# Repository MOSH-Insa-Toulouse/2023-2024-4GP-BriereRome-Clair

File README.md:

# 2023-2024-4GP-BriereRome-Clair
Projet Capteur de Jules et Gabriel 
# Projet Capteur
## Contexte <br>
Nous avons rélalisé ce projet dans le cadre de notre cours de MOSH (Microcontroleur en Open Source Hardware) à l'INSA Toulouse en 4ème année au sein du département de Génie Physique. <br>
L'objectif de ce projet est de tester les caractéristiques d'un capteur de flexion en graphite. <br>
## Somaire
### [1. Présentation Générale](#pg)
### [2. L'électronique analogique](#ea)
### [3. KiCad](KiCad)
### [4. L'Arduino](#dudu)
### [5. L'Application](#app)
### [6. Résultats et datasheet](#res) 

# 1. Présentation Générale <a name="pg">
Voici ci-dessous un schéma de notre projet qui permet de visualiser le lien entre chaque partie. <br>
```mermaid
    graph TD;
    classDef PCB1 fill:pink,color:black,stroke:black;
    classDef App fill:lightblue,color:black,stroke:black;
    B((Carte Arduino))-->Module_BT;
    Boutons-->B((Carte Arduino));
    Ampli-->B((Carte Arduino));
    Potentiomètre -.- OLED;
    Potentiomètre-->Ampli; 
    D[Capteur Graphite]-->Ampli;
    Boutons -.- Potentiomètre;
    B((Carte Arduino))-->Potentiomètre;
    Module_BT -.-> appli;
    B((Carte Arduino))-->OLED;
    A[Flex Sensor]-->B((Carte Arduino));
    PCB
    class Ampli PCB1;
    class Potentiomètre PCB1;
    class Boutons PCB1;
    class OLED PCB1;
    class Module_BT PCB1;
    class Appli App;
    class PCB PCB1;
``` 
Afin de mesurer la flexion de notre capteur graphite nous mesurons sa resistance. Cependant, sa resitance étant très grande, le signal à mesurer est très faible. Nous utilisons donc un amplificateur pour augmenter le signal et qu'il soit ainsi mesurable. Nous utilisons ensuite une carte arduino uno pour mesurer ce signal et le transmettre via bluetooth à une application mobile. Nous utilisons aussi des boutons et un afficheur OLED afin de changer la valeur d'un potententiomètre digital qui module le gain de l'amplificateur. <br>

# 2. L'electronique analogique <a name="ea">
La résistance de notre capteur en graphite varie en fonction de sa flexion. Nous cherchons donc à mesurer les variations de résistance de ce capteur. Cependant il n'y a que des entrée analogique de tension, et les variations de signal sont très petites, il nous faut donc utiliser un circuit amplificateur transimpédence afin d'obtenir une variation de tension mesurable par les convertisseur Analogique-Numérique de l'Arduino.

La résistance du capteur varie en fonction de sa déformation. On impose une tension à ses bornes et on détecte donc une variation de courrant. On fait passer ce courrant dans une résistance de shunt vers la masse, la tension au borne de cette résistance de shunt varie donc avec la déformation du capteur. C'est cette tension que l'on va amplifier.
<br>
Schéma de l'amplificateur : <br>
 <br>
La résistance R2 est remplacée par un potentiomètre digital afin de pouvoir régler le gain de l'amplificateur.

# 3. KiCad : [ici pour les docs](https://github.com/MOSH-Insa-Toulouse/2023-2024-4GP-BriereRome-Clair/tree/main/Shield) <a name="KiCad">
Nous avons réalisé un PCB en utilisant l'application KiCad8. Pour ce faire, nous avons repris le schéma éléctrique decrit ci-dessus. <br>
Nos contraintes etaient les suivantes:
* Largeur de la piste : 0,5 mm minimum
* Isolation des pistes : 0.5mm minimum
* Bluetooth, OLED, Connecteurs (header) : pad à 1mm de diamètre, ovale 2*2.54mm
* Résistance, condensateur, support AOP : Pad à 0.8mm de diamètre, Cercle 2.54mm
* Support AOP, Pot Digital : pad n°1 rectangulaire, les autres ovales ou ronds

Nous avons créé la plupart des emprintes pour les rajouter au PCB. Elles sont disponibles dans nos fichiers. <br>
Une fois le document complété, nous avons imprimé le PCB et avons soudé chacun des composants. <br>
    <br>
   Partie Schématique: <br>
    <br>
   <br>
   Partie PCB : <br>
    <br>

# 4. L'Arduino : [ici pour le code](https://github.com/MOSH-Insa-Toulouse/2023-2024-4GP-BriereRome-Clair/blob/main/Projet_capt.ino) <a name="dudu">
## Présentation générale
Le programme Arduino permet de réaliser 4 fonctions :
* ***Régalage*** du calibre de l'amplificateur avec **3 boutons**
* ***Affichage*** du choix sur un **ecran OLED**
* ***Acquisition*** des mesurese du **flex sensor**
* ***Communication*** vers une appli Android via **bluetooth**
Le code est modulaire, chaque fonctionnalité est assurée par une fonction indépendante.

## Détail sur les bouton
On utilise 3 boutons (+, - et ok) pour choisir la valeur du gain. La boucle générale met assez de temps à s'exécuter pour ne pas avopir à gérer le débouncing des boutons. On a aussi implémenter un timer qui permet que la valeur de change pas trop vite en cas d'appuie long.
Le code utilise 2 variables (valeur séléctionnée et valeur validée)

## Détail sur l'écran
Nous avons utilisé très simplement la librairie ecranOLED

## Détail sur le potentiomètre numérique
Ce composant communique avec le protocole SPI, nous avons donc utilisé la librairie SPI.

## Détail sur l'acquisition des données
Nous avons fait une lecture analogique sur les entrée puis utilisé map pour que les données soient transférable via le module bluetooth en un seul octet.

## Détail sur la communication
Nous avons écrit les données sur un port série relié au module bluetooth.

# 5. L'Application <a name="app">
Afin de communiquer avec l'adruino, nous avons créé une application en utilisant "MIT app inventor".
## Présentation générale
Notre application comporte : <br>
* 2 graphiques :
    * 1 pour le capteur graphite
    * 1 pour le flex sensor
* 2 afficheurs numériques avec des valeurs entre 0 et 255
  * 1 pour le capteur graphite
  * 1 pour le flex sensor
* 1 bouton de sélection Bluetooth
* 1 bouton de reset pour les graphiques
  <br>
    
    <br>
## Partie 1 : Sélection du périphérique Bluetooth
En cliquant sur le bouton "select bluetooth", vous pouvez ouvrir une liste déroulante et selectionner le bluetooth correspondant au module bluetooth utillisé sur le PCB.

## Partie 2 : Reception des données
Le fait de sélectionner un Bluetooth déclenche une horloge qui va séquencer la reception de données. <br>
La boucle de l'horloge verifie si des données sont disponibles. Si il y en a, elle met chacune des deux valeurs (Flex sensor et capteur graphite) dans une variable. <br>

## Partie 3 : Affichage graphique
Afin de rendre les données facilement lisibles, nous avons décidé d'utiliser des graphiques. Pour cela nous avons utilisé les chart2D. <br>
Afin de recentrer automatiquement le graphique, nous attendons d'avoir le bon nombre de mesures et utilisons ensuite la fonction SetDomain pour décaler le graphique. Le bouton reset permet de remettre l'echelle à 0.

# 6. Résultats et datasheet <a name="res">
### Objectifs
Nous avons monté un banc de test afin d'etudier l'influence du type de crayon utilisé sur les performances du capteur et regarder la variation de résistance. <br>
### Méthode
Pour cela nous avons utilisé des cercles de diamètre differnent (2cm, 3cm, 4cm et 5cm). La déformation est calculée selon l'expression suivante : $\varepsilon = \frac{D}{e}$ avec $D$ diamètre du demi-cercle et épaisseur du papier. <br>
Nous avons ensuite exprimé la variation de résistance en fonction de la deformation. <br>
### Résultats
Nous avons obtenu les courbes ci-dessous. Nous observons que la variation est lineaire et que le type de crayon a une forte influence. Les crayons plus durs ("hard") semblent avoir une plus grande sensibilité que les crayons doux. <br>
Ce resultat est le même en compression et en tension. <br>
<br>

<br>
### Datasheet
Afin de synthétiser nos résultats, nous avons fait une datasheet disponible [ici](https://github.com/MOSH-Insa-Toulouse/2023-2024-4GP-BriereRome-Clair/blob/main/Datasheet.docx).

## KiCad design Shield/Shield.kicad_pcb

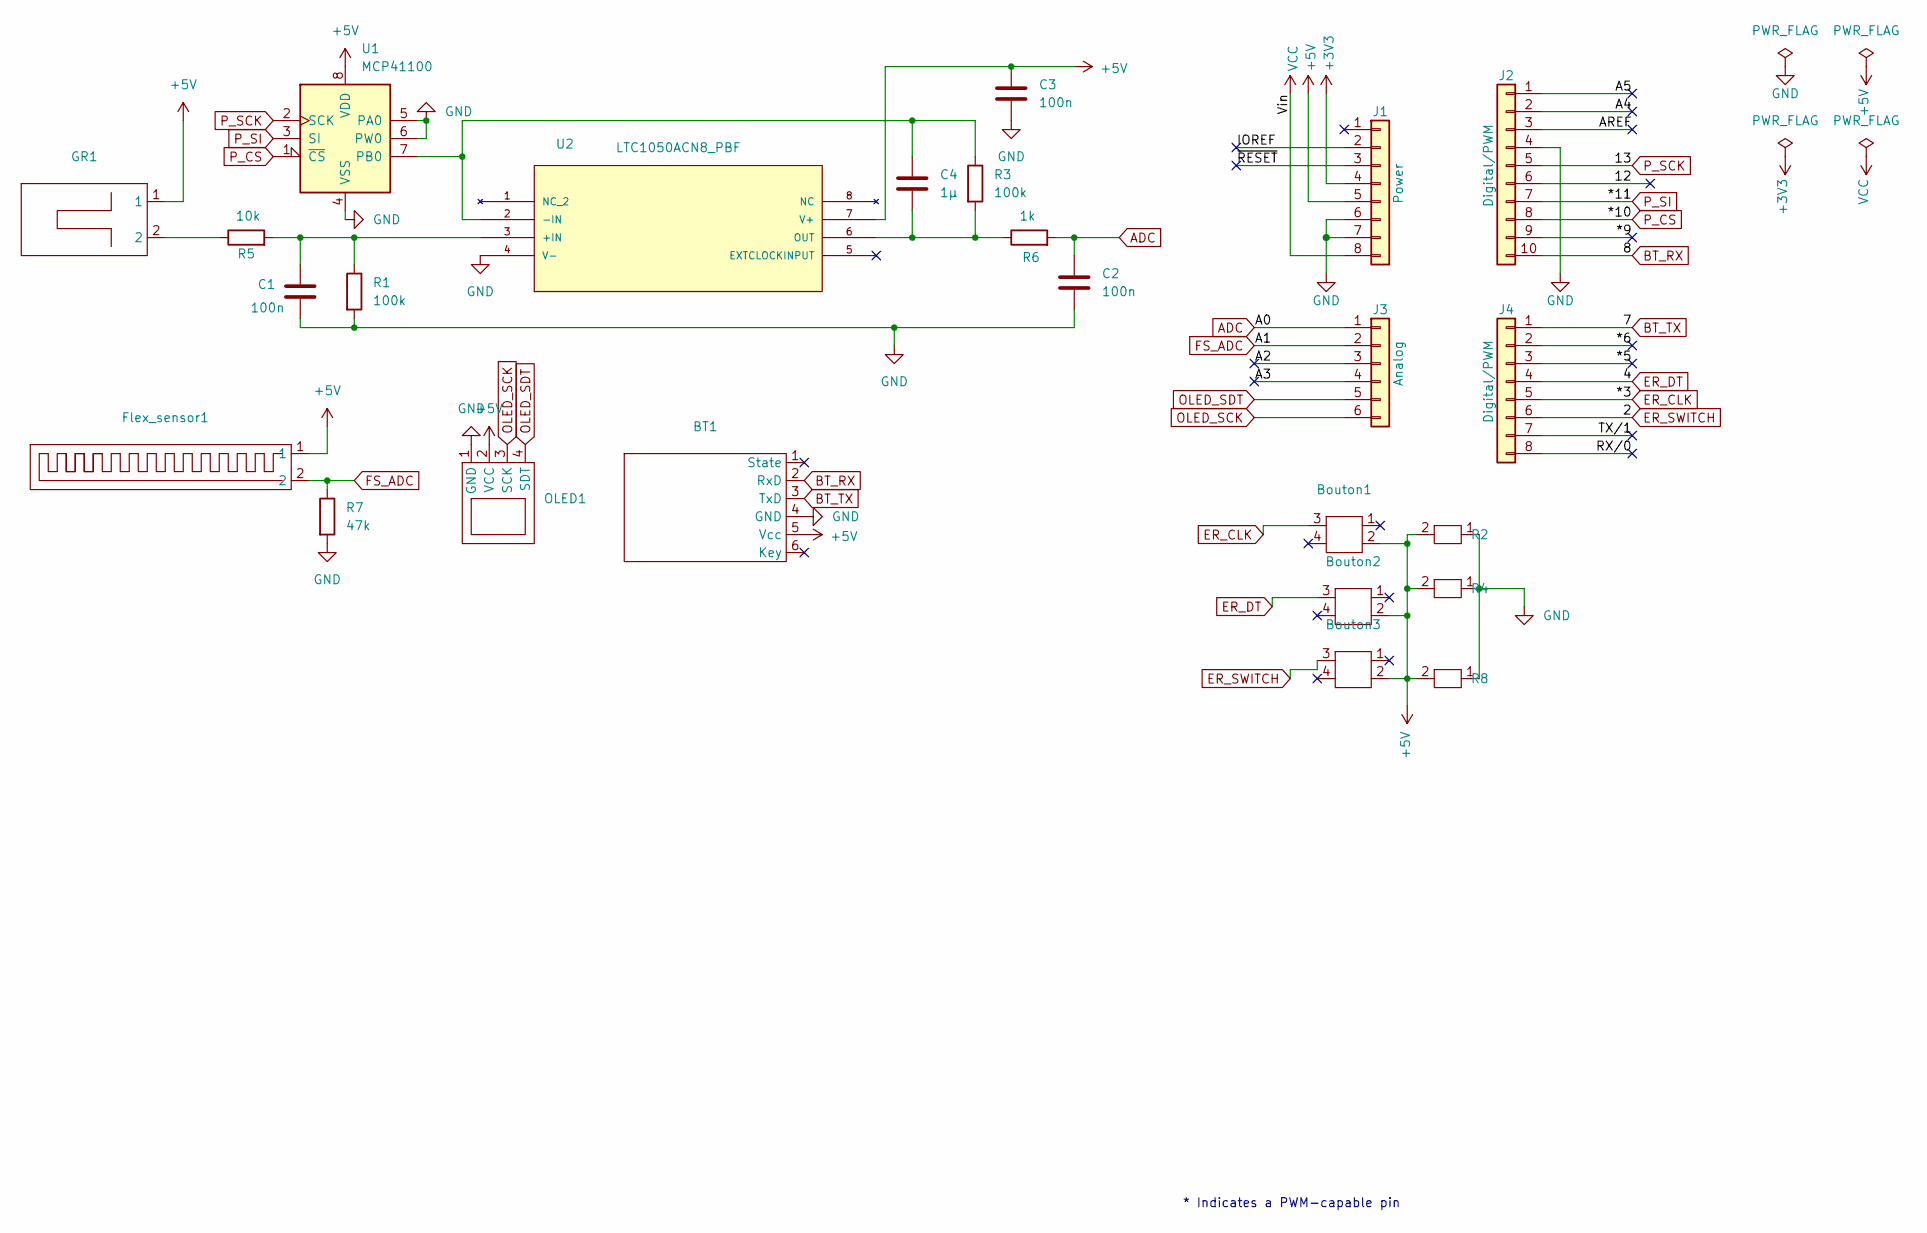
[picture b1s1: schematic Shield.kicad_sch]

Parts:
BT1: HT-05
Bouton1, Bouton2, Bouton3: Bouton
C1, C2, C3: 100n; CP_Radial_Tantal_D4.5mm_P5.00mm
C4: 1µ; C_Rect_L7.2mm_W4.5mm_P5.00mm_FKS2_FKP2_MKS2_MKP2
Flex_sensor1: Flex_Sensor
GR1: Capteur_GR
J1: Power; PinSocket_1x08_P2.54mm_Vertical
J2: Digital/PWM; PinSocket_1x10_P2.54mm_Vertical
J3: Analog; PinSocket_1x06_P2.54mm_Vertical
J4: Digital/PWM; PinSocket_1x08_P2.54mm_Vertical
OLED1: OLED
R1, R3: 100k; R_Axial_DIN0207_L6.3mm_D2.5mm_P10.16mm_Horizontal
R2, R4, R8: Res_debout
R5: 10k; R_Axial_DIN0207_L6.3mm_D2.5mm_P10.16mm_Horizontal
R6: 1k; R_Axial_DIN0207_L6.3mm_D2.5mm_P10.16mm_Horizontal
R7: 47k; R_Axial_DIN0207_L6.3mm_D2.5mm_P10.16mm_Horizontal
U1: MCP41100
U2: LTC1050ACN8_PBF; LTC1050; MANUFACTURER_PART_NUMBER ltc1050acn8

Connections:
+3V3: J1.4
+5V: BT1.5 (Vcc), Bouton1.2, Bouton2.2, Bouton3.2, C3.1, Flex_sensor1.1, GR1.1, J1.5, OLED1.2 (VCC), R2.2, R4.2, R8.2, U1.8 (VDD), U2.7 (V+)
/12: J2.6
/*5: J4.3
/*6: J4.2
/*9: J2.9
/A2: J3.3
/A3: J3.4
/A4: J2.2
/A5: J2.1
/AREF: J2.3
/IOREF: J1.2
/RX/0: J4.8
/TX/1: J4.7
/~RESET: J1.3
ADC: C2.1, J3.1, R6.2
BT_RX: BT1.2 (RxD), J2.10
BT_TX: BT1.3 (TxD), J4.1
ER_CLK: Bouton1.3, J4.5
ER_DT: Bouton2.3, J4.4
ER_SWITCH: Bouton3.3, J4.6
FS_ADC: Flex_sensor1.2, J3.2, R7.1
GND: BT1.4 (GND), C1.2, C2.2, C3.2, J1.6, J1.7, J2.4, OLED1.1 (GND), R1.2, R2.1, R4.1, R7.2, R8.1, U1.4 (VSS), U1.5 (PA0), U1.6 (PW0), U2.4 (V-)
unnamed: GR1.2, R5.1
unnamed: C4.1, R3.1, U1.7 (PB0), U2.2 (-IN)
unnamed: C1.1, R1.1, R5.2, U2.3 (+IN)
unnamed: C4.2, R3.2, R6.1, U2.6 (OUT)
OLED_SCK: J3.6, OLED1.3 (SCK)
OLED_SDT: J3.5, OLED1.4 (SDT)
P_CS: J2.8, U1.1 (~CS)
P_SCK: J2.5, U1.2 (SCK)
P_SI: J2.7, U1.3 (SI)
VCC: J1.8

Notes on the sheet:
* Indicates a PWM-capable pin

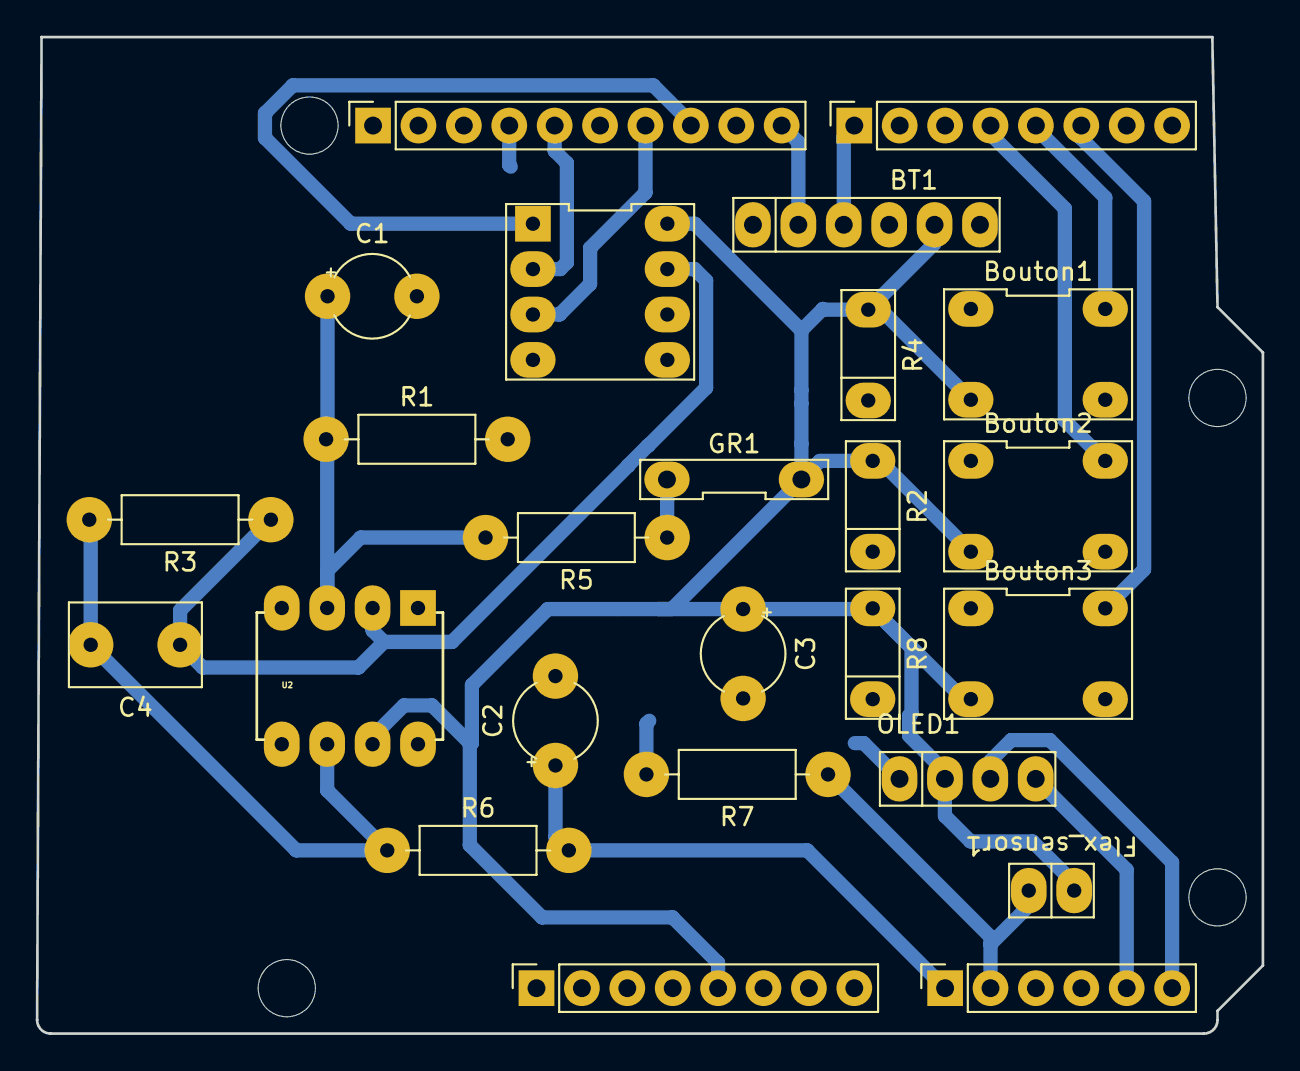
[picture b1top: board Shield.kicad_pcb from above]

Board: 2 copper layers, 68.6 x 55.8 mm, 29 parts (0 on the bottom side), 18 nets.

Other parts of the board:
MH1, MH2, MH3, MH4: MountingHole_3.2mm

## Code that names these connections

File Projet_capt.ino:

#include <Adafruit_SSD1306.h>
#include <SPI.h>
#include <SoftwareSerial.h>

// definition des pins
// Potar digital 
#define P_SCK 13
#define P_CS  10 
#define P_SI  11 
// Module Bluetooth
#define BT_RX 8
#define BT_TX 7 
#define BT_baudrate 9600
SoftwareSerial BT_Serial(BT_TX, BT_RX); // Tx et Rx du module bt


// Boutons 
#define B_plus  3 
#define B_moins 4 
#define B_ok    2 
#define B_time  300
// Cateurs graphite et flex sensor
#define GR_ADC A0 
#define FS_ADC A1 
// Ecran oled
#define OLED_SDT A4 
#define OLED_SCK A5 

//ECRAN OLED
#define oled_largeur     128
#define oled_hauteur     64
#define brocheResetOLED  -1
#define addI2C_oled      0x3C
int OLED_ok = 0 ;
Adafruit_SSD1306 ecranOLED(oled_largeur,oled_hauteur,&Wire,brocheResetOLED);

// BOUTONS ET SELECTION DU CALIBRE
int read_B_plus;
int last_B_plus_state;
int read_B_moins;
int last_B_moins_state;
int read_B_ok;
int last_B_ok_state;
int milli_B =0;
int Val_select = 1; 
int Val_choisie = 1;
int choix_modifie = 0;

// Potar digital

#define MCP_WRITE 0b00010001
#define P_Rmax  50 // Rmax en kOhm
#define R3      100 // en kOhm
float R_cible = 0 ;
int P_pos = 0 ;

// Capteurs
float GR_val = 0 ;
float FS_val = 0 ;






void boutons(){
  int read_B_plus = digitalRead(B_plus);
  if ((read_B_plus == HIGH) && (millis() - milli_B > B_time)){
      Val_select++ ;
      milli_B = millis();
    }

  int read_B_moins = digitalRead(B_moins);
  if  ((read_B_moins == HIGH) && (millis() - milli_B > B_time)){
      Val_select-- ;
      milli_B = millis();
    }

  int read_B_ok = digitalRead(B_ok);
  if  (read_B_ok == HIGH){
      Val_choisie = Val_select ;
      choix_modifie = 1 ;
  } 
  last_B_plus_state = read_B_plus ;
  last_B_moins_state = read_B_moins ;
  last_B_ok_state = read_B_ok ;
}

void AffichageOLED(int vs, int vc){
    ecranOLED.clearDisplay();
    ecranOLED.setCursor(0,0);
    ecranOLED.print("val select : ");
    ecranOLED.println(vs);
    ecranOLED.print("val choisie : ");
    ecranOLED.println(vc);  
    ecranOLED.display();
}

void SPIWrite(int Val){
  SPI.beginTransaction(SPISettings(14000000, MSBFIRST, SPI_MODE0)); 
  
  digitalWrite(P_CS, LOW); // SS pin low to select chip
  
  SPI.transfer(MCP_WRITE);        // Send command code
  SPI.transfer(Val);       // Send associated value
  
  digitalWrite(P_CS, HIGH);// SS pin high to de-select chip
  SPI.endTransaction();
}

void setup() {
  if(ecranOLED.begin(SSD1306_SWITCHCAPVCC, addI2C_oled)) {
    OLED_ok=1;
    ecranOLED.clearDisplay();
    ecranOLED.setTextSize(2);
    ecranOLED.setTextColor(SSD1306_WHITE, SSD1306_BLACK);
    ecranOLED.setCursor(0,0);
    ecranOLED.println("OLED OK");
    ecranOLED.display();   
    delay(2000);
    ecranOLED.clearDisplay();
  }

  pinMode (P_SI,INPUT);
  pinMode (BT_TX,INPUT);
  pinMode (B_plus,INPUT);
  pinMode (B_moins,INPUT);
  pinMode (B_ok,INPUT);
  pinMode (P_SI,INPUT);
  pinMode (GR_ADC,INPUT);
  pinMode (FS_ADC,INPUT);

  digitalWrite(P_CS, HIGH); //desactive le chip select du potar
  SPI.begin();
  SPIWrite(1);

  BT_Serial.begin(BT_baudrate);
  //BT_Serial.println("BT ok");

  Serial.begin(9600);
  Serial.println("start");
}

void loop() {
  //Gestion des boutons
  boutons();
  // Gestion de l'OLED
  if (OLED_ok){
    AffichageOLED(Val_select, Val_choisie);
  }

  // Gestion du potar
  /* Mettre le potar à la valeur qui correspond au gain valchoisie si elle a bougé
  G = (R2+R3)/R2 <=> R2 * G = R2+R3 <=> R2(G-1)=R3 <=> R2 = R3/(G-1)*/
  if (choix_modifie){
    R_cible = R3/(Val_choisie-1);
    P_pos = R_cible*256/P_Rmax ;    // pour choisir le gain
    //P_pos = Val_choisie*256/P_Rmax ;  // pour choisir la valeur de la résistance
    P_pos = constrain(P_pos, 0, 255);
    
    SPIWrite(P_pos);
    choix_modifie = 0 ;
  }

  //Mesures
  GR_val=analogRead(GR_ADC);
  FS_val = analogRead(FS_ADC);

  FS_val=map(FS_val,0,1023,0,255);
  GR_val=map(GR_val,0,1023,0,255); 

  //Bluetooth
  BT_Serial.write(FS_val);
  BT_Serial.write(GR_val);
  
  /*Serial.print(FS_val);
  Serial.print("; ");
  Serial.println(GR_val);*/

  delay(40);

}

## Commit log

2024-06-05 Rename Capture d'écran 2024-04-22 193551.png to ElecAna

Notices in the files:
parts and their libraries:
COPYRIGHT: Copyright C 2016 Accelerated Designs. All rights reserved
